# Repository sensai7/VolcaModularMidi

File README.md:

# VolcaModularMidi
This is a hardware mod to add MIDI IN capability to the [Korg Volca Modular](https://www.korg.com/us/products/dj/volca_modular/)

## Schematic

## Bill Of Materials:
 * R1  220 ohm resistor
 * R2  270 ohm resistor
 * D1  1N4148 diode
 * J1  2.54mm header
 * J2  DIN-5 connector
 * U1  6n139 optocoupler (6n138 and 6n137 should also work as well)

## How to install:

BEFORE YOU BEGIN: 

* This installation process requires you to open your Korg volca Modular, most likely voiding the warranty. The creator of this mod and all the contributors of this project are not to be held responsible for possible malfunctions caused by this process.

* In these example photos the mod was already installed (the red/orange/yellow/green cables), but I repeated the process to take the photos and make it easier to explain.

* Read the tutorial and make sure you understand all the steps before proceeding.

Be sure to have the following tools:
  * M3 screwdriver
  * Flat screwdriver (not absolutely necessary but it's useful to unplug the ribbon connectors)
  * Pliers or something to snip and cut thin cables
  * A dril or any tool to open a hole in the case

1-	Unscrew the screws from the back.

2-	Gently pull from a potentiometer to detach the blue case from the circuit.

3-	Unplug the batteries connector (red/black cables) in the top right of the board

4-	Lay the circuit down, be careful with the speaker connection (orange/brown cables)

5-	You can see the holes now, they're labelled as MIDI_RX, MIDI_TX, +3.3V, GND

6-	Unpeel the black tape and unplug the keyboard connector (white/orange cables)

7-	Unscrew the 6 screws attaching the main board with the keyboard board.

8-	Sit the main board on it's place in the blue case and open a hole on the right side enough to let the four cables go through. Then solder the four cables facing down and snip the excess wire. (disregard the quality of mine, I don't have the tools nor skill for these things :( )

9-	Repeat the process from steps 7 to 1 in inverse order to reassemble the unit.

## Mod mods

If you have the tools, and patience, you can glue the female connections to the case so you can plug it directly (here's a poorly photoshopped concept illustrating it)

If you prefer to use a 3.5mm stereo jack instead of the big DIN-5 connector, here's another poorly photoshopped concept

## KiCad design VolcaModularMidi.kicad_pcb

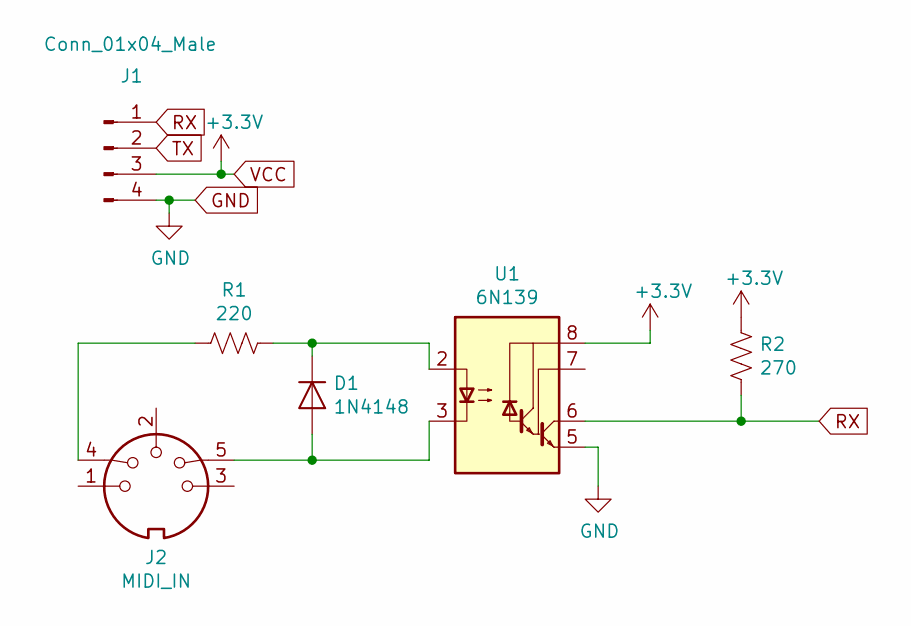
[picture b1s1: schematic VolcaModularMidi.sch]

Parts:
D1: 1N4148; D_DO-35_SOD27_P7.62mm_Horizontal
J1: Conn_01x04_Male; PinHeader_1x04_P2.54mm_Vertical
J2: MIDI_IN; din-5
R1: 220; R_Axial_DIN0207_L6.3mm_D2.5mm_P7.62mm_Horizontal
R2: 270; R_Axial_DIN0207_L6.3mm_D2.5mm_P7.62mm_Horizontal
U1: 6N139; DIP-8_W7.62mm

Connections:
GND: J1.4, U1.5 (GND)
unnamed: D1.1 (K), R1.1, U1.2 (C1)
unnamed: D1.2 (A), J2.5, U1.3 (C2)
unnamed: J2.4, R1.2
RX: J1.1, R2.2, U1.6 (VO2)
TX: J1.2
VCC: J1.3, R2.1, U1.8 (VCC)

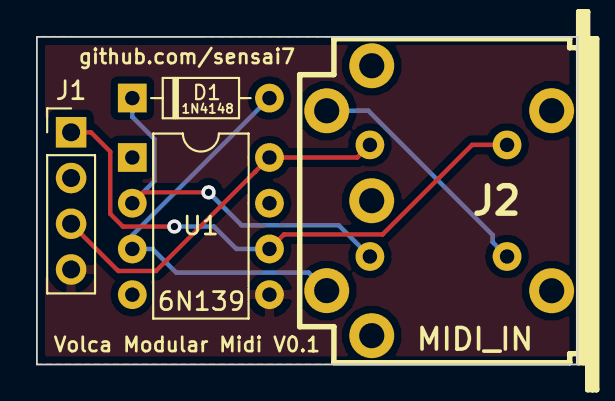
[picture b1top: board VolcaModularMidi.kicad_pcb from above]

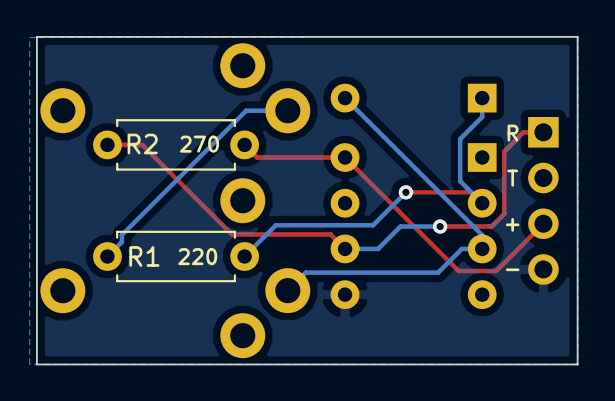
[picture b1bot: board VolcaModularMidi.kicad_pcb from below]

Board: 2 copper layers, 30.0 x 18.2 mm, 6 parts (2 on the bottom side), 6 nets.

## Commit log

2019-05-06 Version 0.1 finished
2019-05-06 adjusted silkscreen
2019-05-23 Added a pic
2019-05-25 Added installation tutorial
2019-06-07 added jack option
2020-05-02 Added Schematic
2020-05-02 im an idiot
